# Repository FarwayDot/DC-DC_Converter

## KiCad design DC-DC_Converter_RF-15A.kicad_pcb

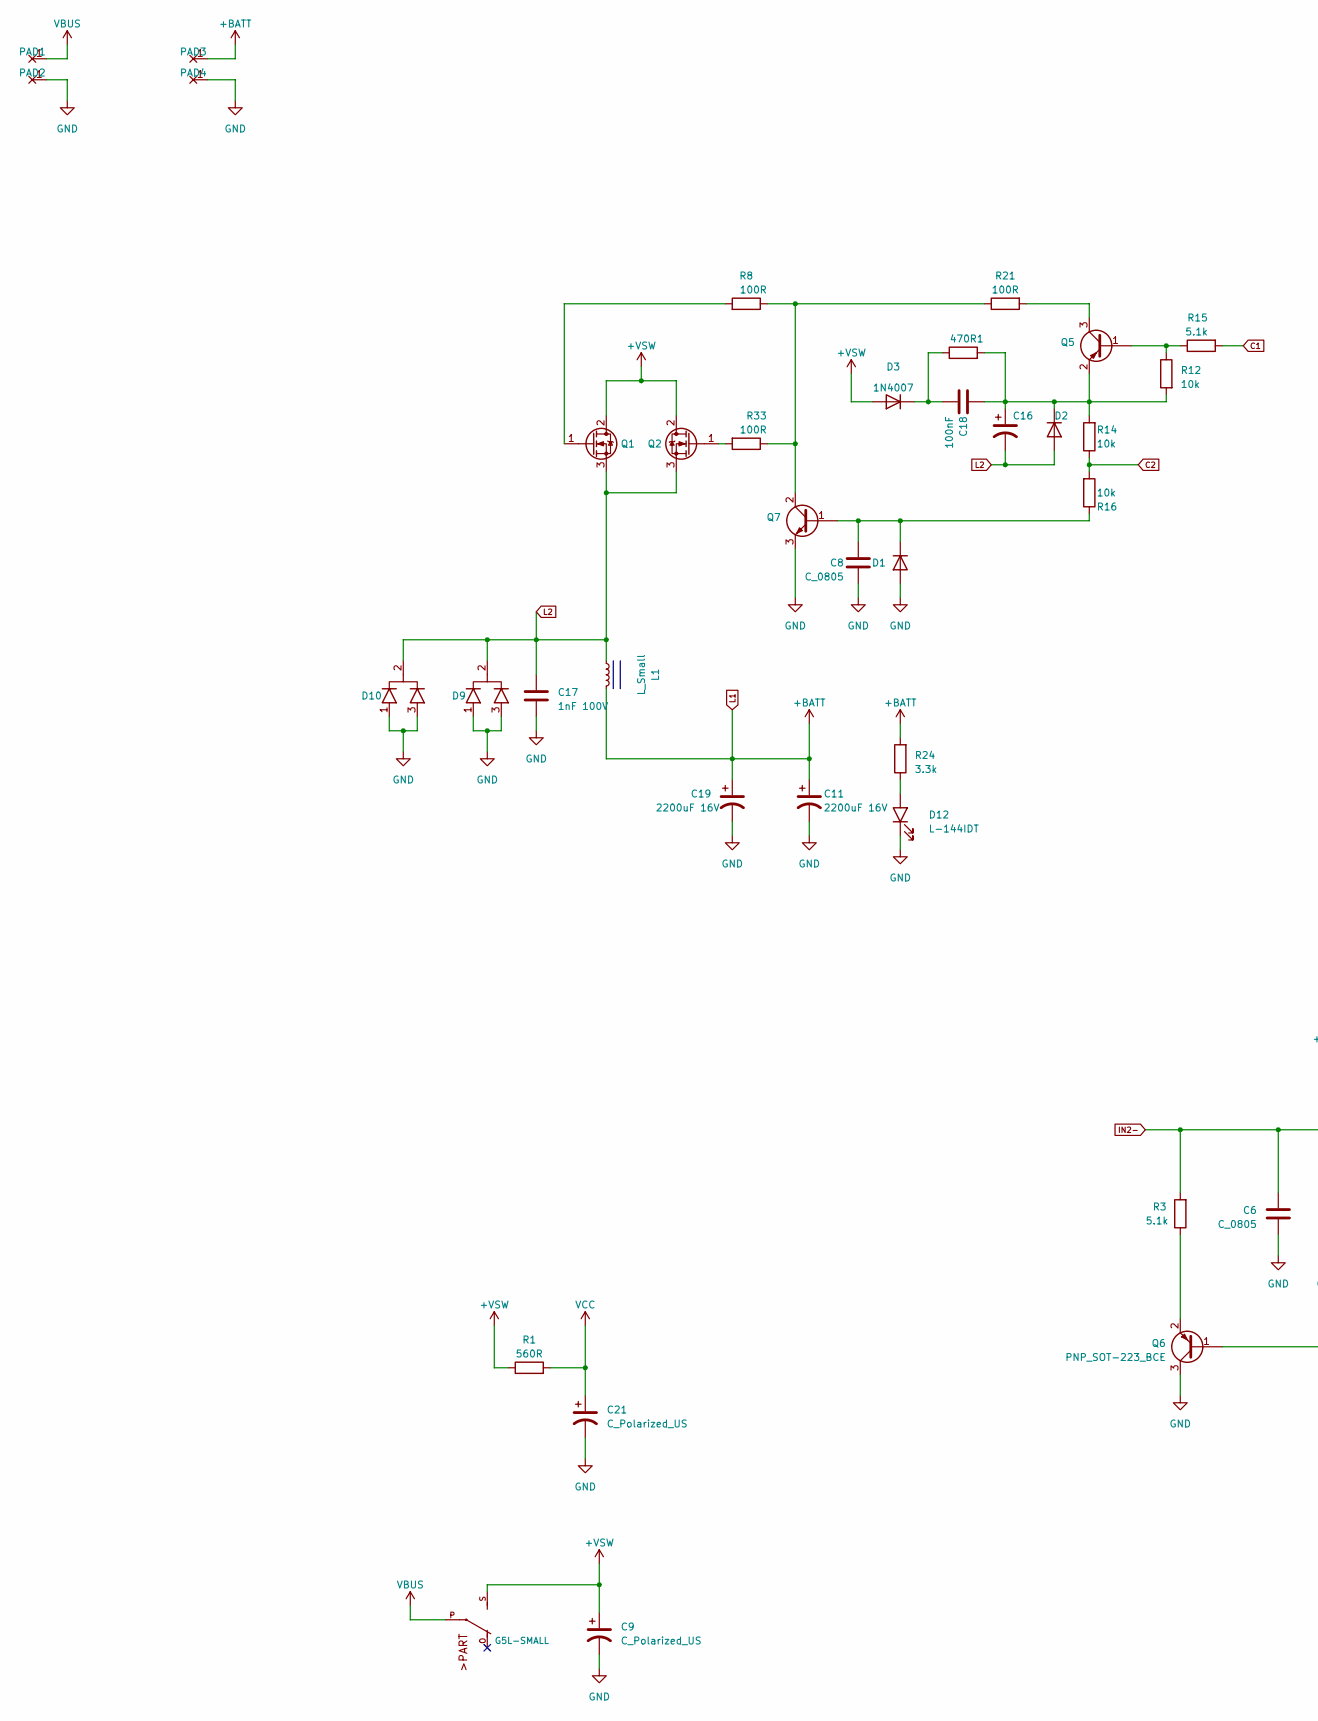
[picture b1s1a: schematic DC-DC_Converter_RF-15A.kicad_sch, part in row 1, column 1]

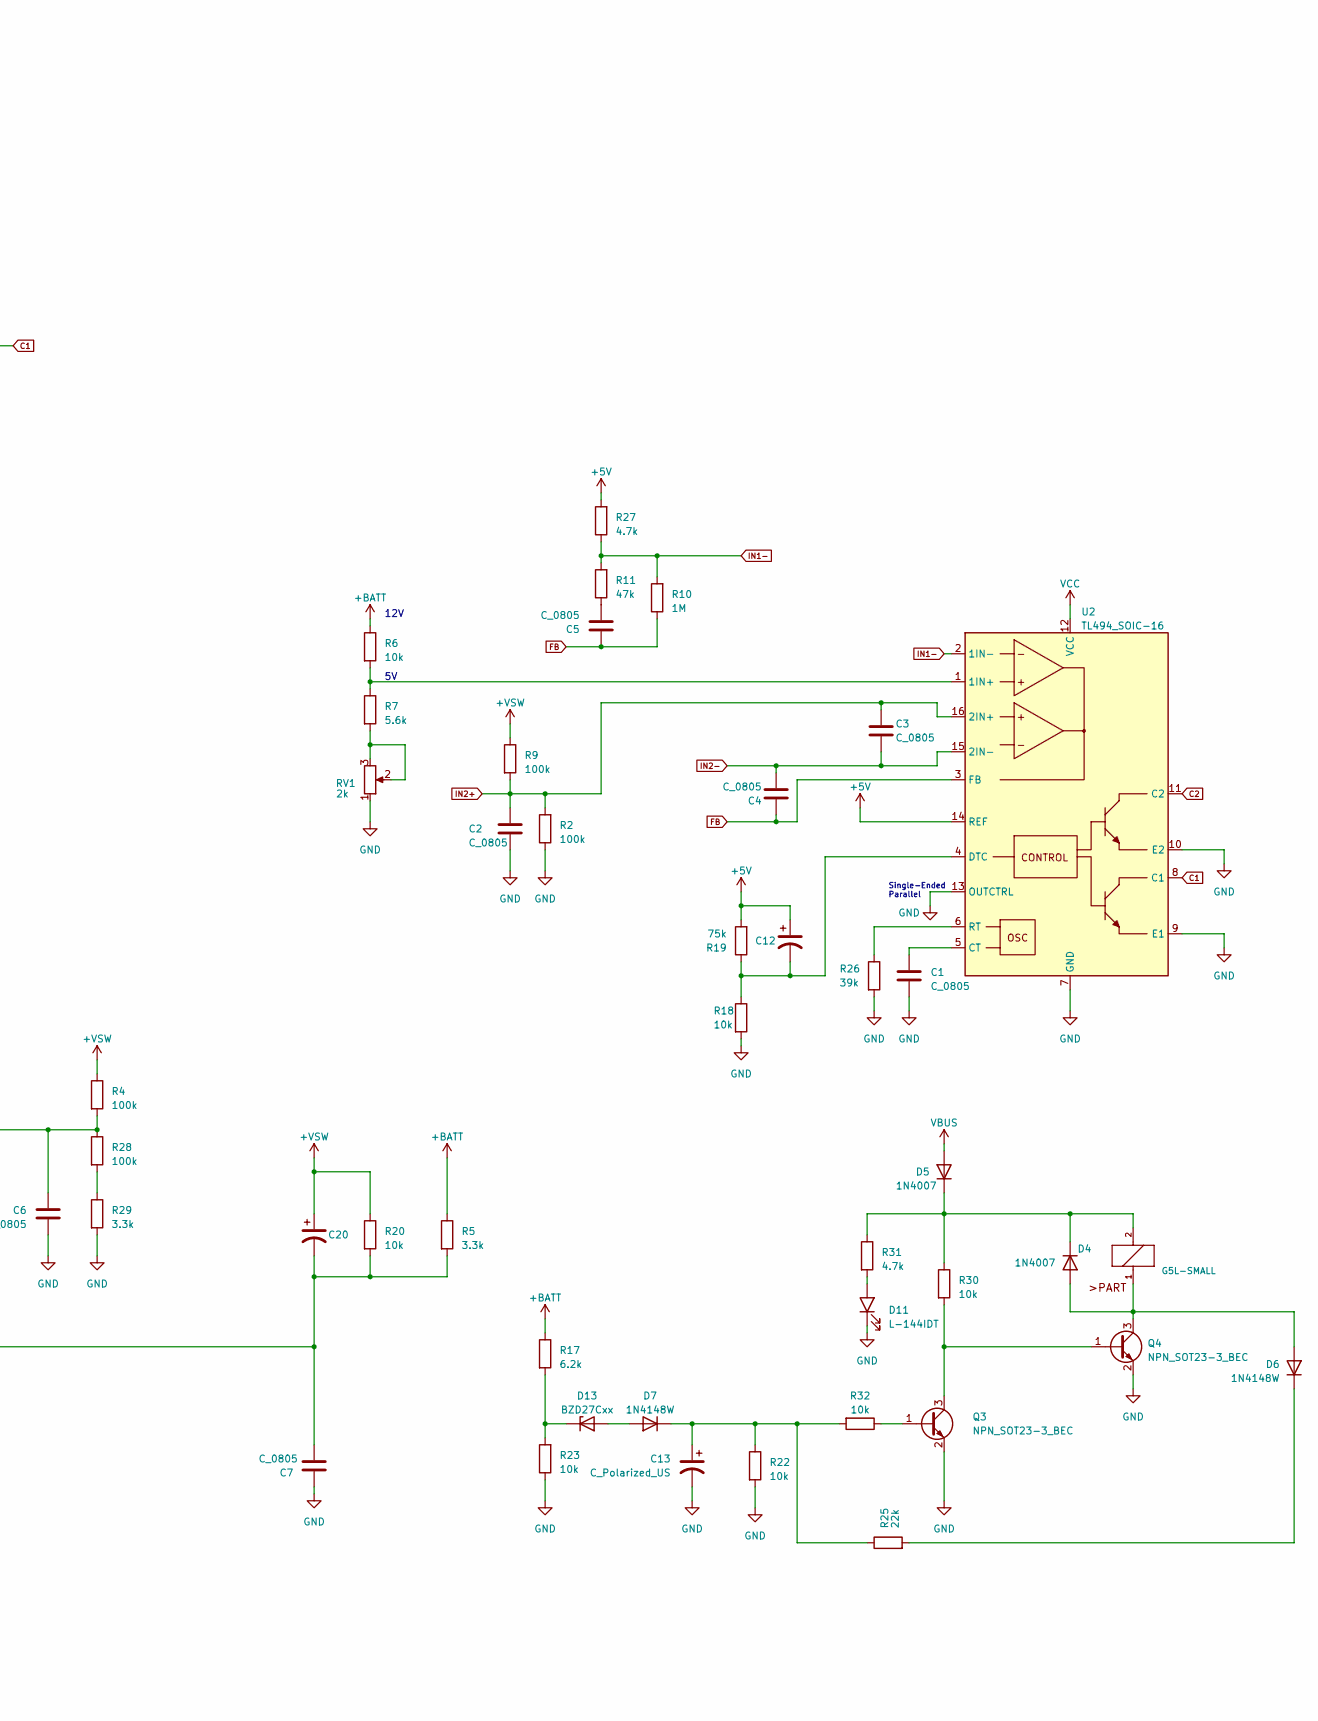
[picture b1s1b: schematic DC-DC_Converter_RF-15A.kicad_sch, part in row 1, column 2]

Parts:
470R1: R_Axial_DIN0414_L11.9mm_D4.5mm_P15.24mm_Horizonta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; R_Axial_DIN0414_L11.9mm_D4.5mm_P15.24mm_Horizontal_1W
C1, C2, C3, C4, C5, C6, C7, C8: C_0805; C_0805_2012Metric
C9: C_Polarized_US; CP_Radial_D13.0mm_P7.50mm
C11, C19: 2200uF 16V; CP_Radial_D10.0mm_P5.00mm
C12, C13, C16: C_Polarized_US; CP_Radial_D5.0mm_P2.50mm
C17: 1nF 100V; C_Rect_L7.2mm_W3.5mm_P5.00mm_FKS2_FKP2_MKS2_MKP2
C18: 100nF; C_Rect_L7.2mm_W3.5mm_P5.00mm_FKS2_FKP2_MKS2_MKP2
C20, C21: C_Polarized_US; CP_Radial_D6.3mm_P2.50mm
D1, D6, D7: 1N4148W; D_SOD-123
D2: 1N4148; D_DO-35_SOD27_P7.62mm_Horizontal
D3, D4, D5: 1N4007; D_DO-41_SOD81_P10.16mm_Horizontal
D9, D10: MBR20100; TO-220-3_Vertical
D11, D12: L-144IDT; LED_3.9x1.9mm
D13: BZD27Cxx; D_SMF
K1: G5L-SMALL; G5LE-SMALL
L1: L_Small; L_Toroid_Vertical_L33.0mm_W17.8mm_P12.70mm_Pulse_KM-5
PAD1, PAD2, PAD3, PAD4: PAD_2.0_1.1
Q1, Q2: 75NF75_TO-220; TO-220-3_Vertical
Q3, Q4: NPN_SOT23-3_BEC; SOT-23-BEC
Q5, Q6: PNP_SOT-223_BCE; SOT-23-BEC
Q7: PXT2222A_SOT-89; SOT-89-3
R1: 560R; R_0805_2012Metric
R2, R4, R9, R28: 100k; R_0805_2012Metric
R3, R15: 5.1k; R_0805_2012Metric
R5, R24, R29: 3.3k; R_0805_2012Metric
R6, R12, R14, R16, R18, R20, R22, R23, R30, R32: 10k; R_0805_2012Metric
R7: 5.6k; R_0805_2012Metric
R8, R21, R33: 100R; R_0805_2012Metric
R10: 1M; R_0805_2012Metric
R11: 47k; R_0805_2012Metric
R17: 6.2k; R_0805_2012Metric
R19: 75k; R_0805_2012Metric
R25: 22k; R_0805_2012Metric
R26: 39k; R_0805_2012Metric
R27, R31: 4.7k; R_0805_2012Metric
RV1: 2k; Potentiometer_Vishay_T73YP_Vertical
U2: TL494_SOIC-16; SOIC-16_4.55x10.3mm_P1.27mm

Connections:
+5V: C12.1, R19.2, R27.2, U2.14 (REF)
+VSW: C9.1, C20.1, D3.2 (A), K1.S, Q1.2 (D), Q2.2 (D), R1.1, R4.1, R9.1, R20.1
C1: R15.2, U2.8 (C1)
C2: R14.1, R16.2, U2.11 (C2)
FB: C4.2, C5.1, R10.1, U2.3 (FB)
GND: C1.2, C2.1, C6.2, C7.1, C8.2, C9.2, C11.2, C13.2, C17.2, C19.2, C21.2, D1.2 (A), D9.1 (A), D9.3 (A), D10.1 (A), D10.3 (A), D11.K, D12.K, PAD2.1, PAD4.1, Q3.2 (E), Q4.2 (E), Q6.3 (C), Q7.3 (E), R2.1, R18.2, R22.2, R23.1, R26.2, R29.2, RV1.1, U2.7 (GND), U2.9 (E1), U2.10 (E2), U2.13 (OUTCTRL)
IN1-: R10.2, R11.2, R27.1, U2.2 (1IN-)
IN2+: C2.2, C3.1, R2.2, R9.2, U2.16 (2IN+)
IN2-: C3.2, C4.1, C6.1, R3.2, R4.2, R28.1, U2.15 (2IN-)
L1: C11.1, C19.1, L1.2, PAD3.1, R5.1, R6.1, R17.1, R24.2
L2: C16.2, C17.1, D2.2 (A), D9.2 (K), D10.2 (K), L1.1, Q1.3 (S), Q2.3 (S)
unnamed: C5.2, R11.1
unnamed: C8.1, D1.1 (K), Q7.1 (B), R16.1
unnamed: 470R1.2, C16.1, C18.2, D2.1 (K), Q5.2 (E), R12.2, R14.2
unnamed: 470R1.1, C18.1, D3.1 (K)
unnamed: D4.2 (A), D6.2 (A), K1.1, Q4.3 (C)
unnamed: D4.1 (K), D5.1 (K), K1.2, R30.1, R31.1
unnamed: D6.1 (K), R25.2
unnamed: C13.1, D7.1 (K), R22.1, R25.1, R32.2
unnamed: D11.A, R31.2
unnamed: D12.A, R24.1
unnamed: D7.2 (A), D13.2 (A)
unnamed: D13.1 (K), R17.2, R23.2
unnamed: Q1.1 (G), R8.2
unnamed: Q2.1 (G), R33.2
unnamed: Q3.1 (B), R32.1
unnamed: Q3.3 (C), Q4.1 (B), R30.2
unnamed: Q5.1 (B), R12.1, R15.1
unnamed: Q5.3 (C), R21.2
unnamed: C7.2, C20.2, Q6.1 (B), R5.2, R20.2
unnamed: Q6.2 (E), R3.1
unnamed: Q7.2 (C), R8.1, R21.1, R33.1
unnamed: R7.2, RV1.2, RV1.3
unnamed: R28.2, R29.1
unnamed: R6.2, R7.1, U2.1 (1IN+)
unnamed: C1.1, U2.5 (CT)
unnamed: C12.2, R18.1, R19.1, U2.4 (DTC)
unnamed: R26.1, U2.6 (RT)
VBUS: D5.2 (A), K1.P, PAD1.1
VCC: C21.1, R1.2, U2.12 (VCC)

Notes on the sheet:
Single-Ended Parallel
12V

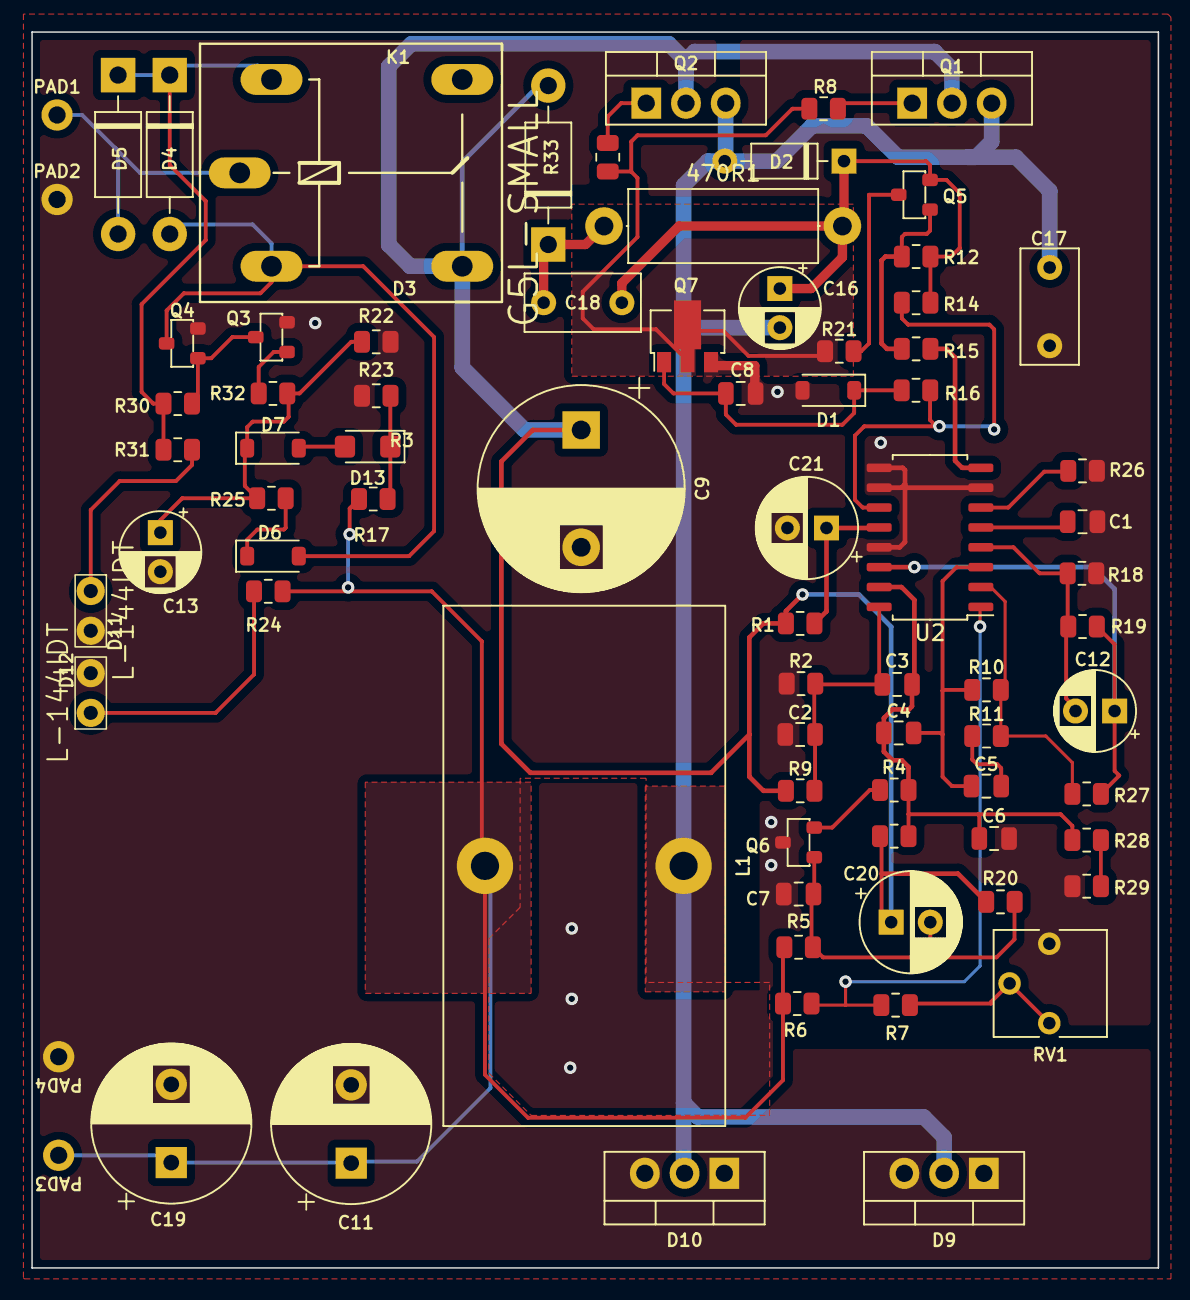
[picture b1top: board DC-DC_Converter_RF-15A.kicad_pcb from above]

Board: 2 copper layers, 72.0 x 79.0 mm, 78 parts (0 on the bottom side), 40 nets.

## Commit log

2024-01-16 PrimerCommit
2024-01-17 Avance 16_01_2024
2024-01-17 Se termina la PCB, queda acomodar el esquemático
2024-01-17 Se añadieron los valores de algunos componentes, falta ordenar
